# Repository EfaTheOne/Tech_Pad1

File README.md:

# Tech_Pad1
My Macropad has 2 neopixels, 6 keys and 1 microcontroller. It will be used for gaming!

This is the screenshot of my Macropad in Fusion.

The schematic has 6 keys and 2 neopixels.

The PCB design was very fun to make, and learning how to make the connections and everything was a huge learning opportunity 

The case fits together using the M3 16mm bolts and was built using only the Tutorial.  

# BOM
6 MK Switch

6 Blank Keycaps

Seeed XIAO RP2040

6 SK6812 MINI-E LED

TechPad1 PCB

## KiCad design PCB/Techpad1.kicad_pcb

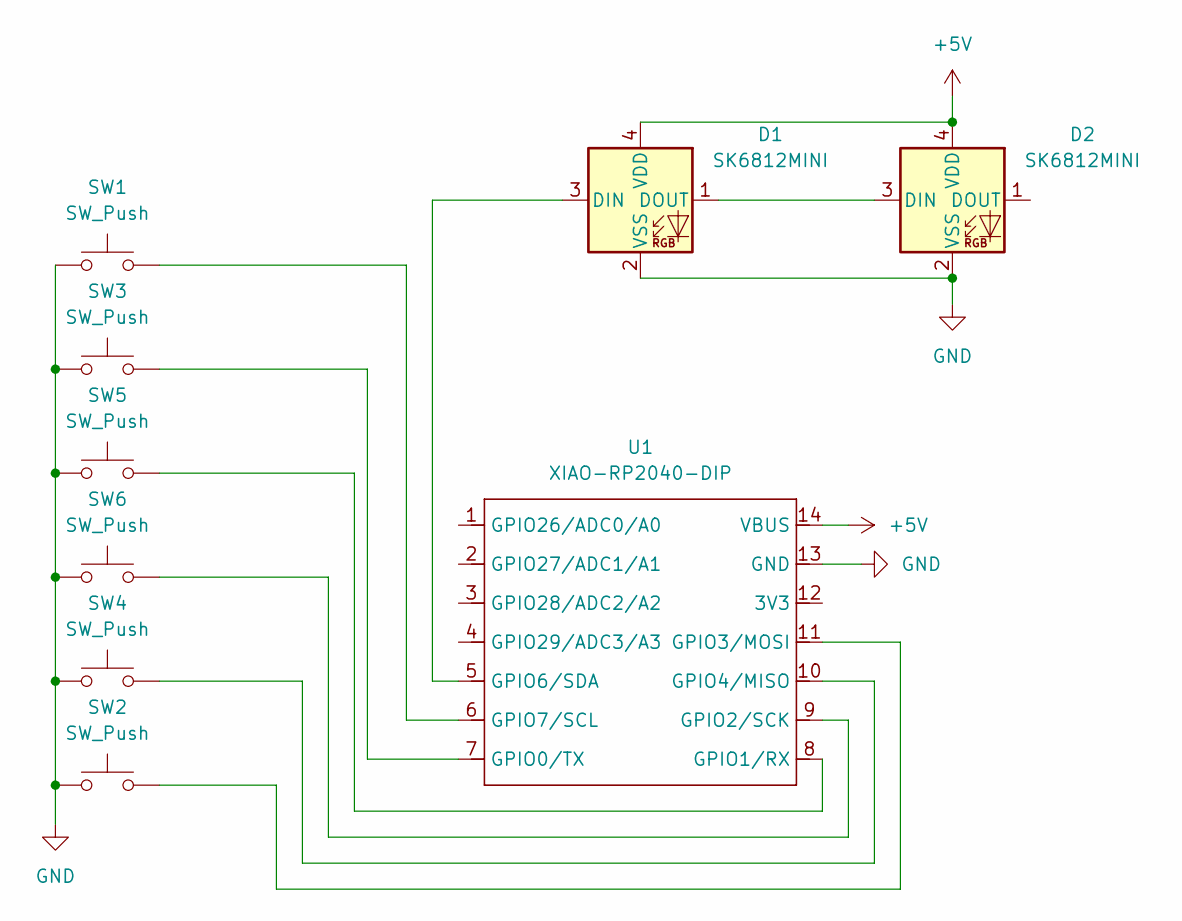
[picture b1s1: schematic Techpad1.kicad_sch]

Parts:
D1, D2: SK6812MINI; LED_SK6812MINI_PLCC4_3.5x3.5mm_P1.75mm
SW1, SW2, SW3, SW4, SW5, SW6: SW_Push; SW_Cherry_MX_1.00u_PCB
U1: XIAO-RP2040-DIP

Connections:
+5V: D1.4 (VDD), D2.4 (VDD), U1.14 (VBUS)
GND: D1.2 (VSS), D2.2 (VSS), SW1.1, SW2.1, SW3.1, SW4.1, SW5.1, SW6.1, U1.13 (GND)
unnamed: D1.3 (DIN), U1.5 (GPIO6/SDA)
unnamed: D1.1 (DOUT), D2.3 (DIN)
unnamed: SW3.2, U1.7 (GPIO0/TX)
unnamed: SW5.2, U1.8 (GPIO1/RX)
unnamed: SW6.2, U1.9 (GPIO2/SCK)
unnamed: SW2.2, U1.11 (GPIO3/MOSI)
unnamed: SW4.2, U1.10 (GPIO4/MISO)
unnamed: SW1.2, U1.6 (GPIO7/SCL)

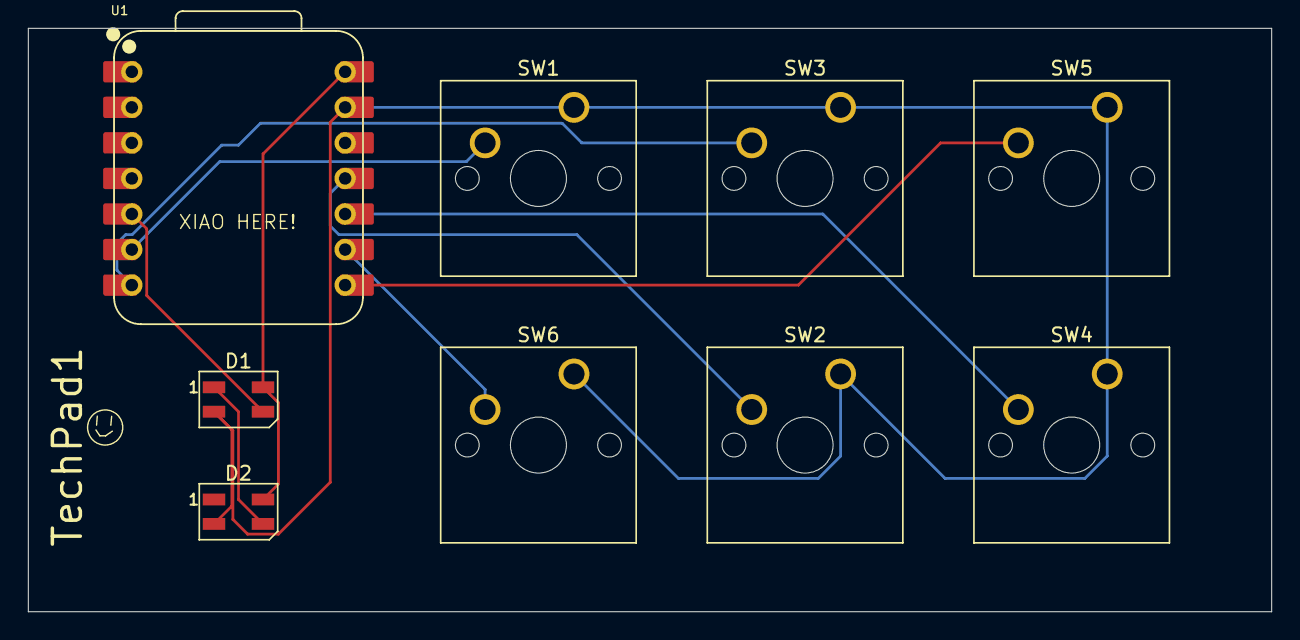
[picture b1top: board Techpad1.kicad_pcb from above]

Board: 2 copper layers, 88.8 x 41.7 mm, 9 parts (0 on the bottom side), 10 nets.

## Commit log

2025-12-04 Create Schematic
2025-12-04 Create file
2025-12-04 Create KMK file code for TechPad1
2025-12-04 Update KMK file code for TechPad1
2025-12-04 Rename KMK file code for TechPad1 to KMK file code for TechPad1.py
